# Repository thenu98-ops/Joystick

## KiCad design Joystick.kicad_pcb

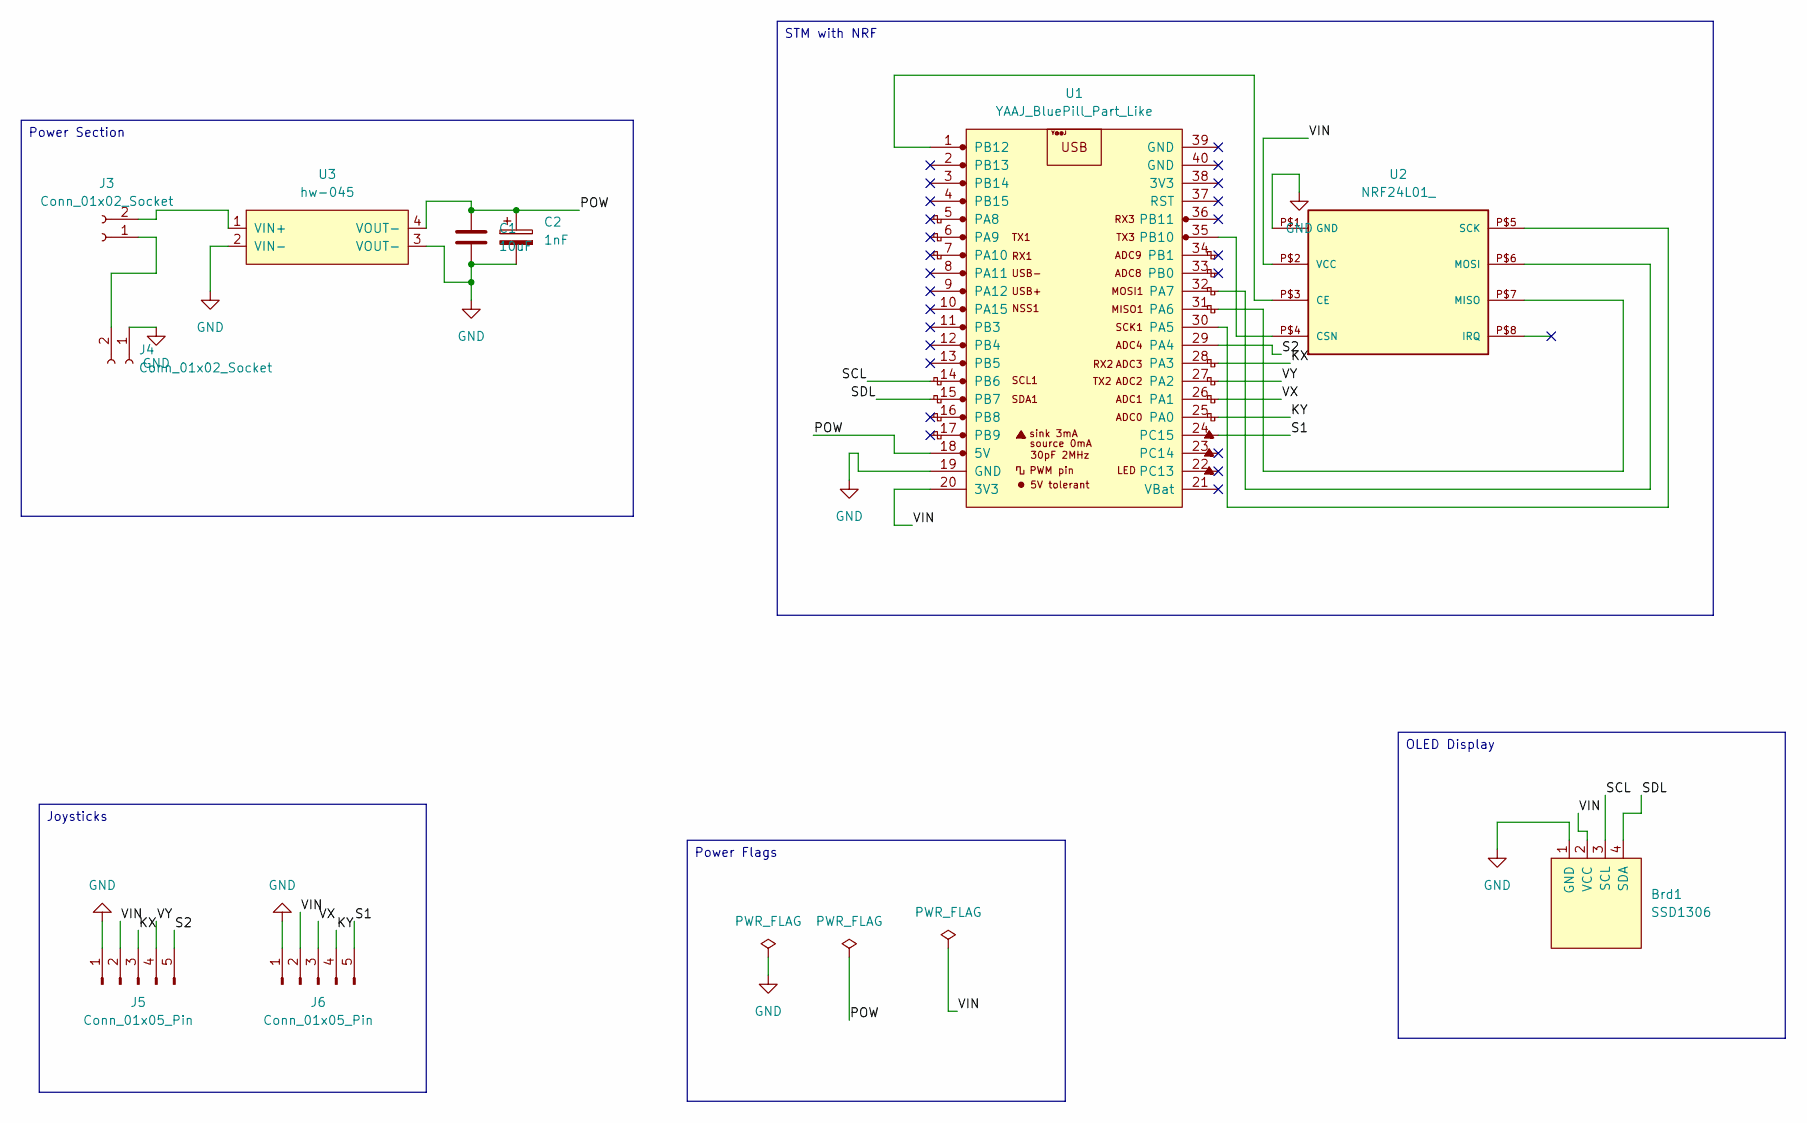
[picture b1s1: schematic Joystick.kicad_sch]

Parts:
Brd1: SSD1306; 128x64OLED
C1: 10uF; CP_Elec_4x5.4
C2: 1nF; CP_Radial_D4.0mm_P1.50mm
J3, J4: Conn_01x02_Socket; PinHeader_1x02_P2.54mm_Horizontal
J5, J6: Conn_01x05_Pin; PinHeader_1x05_P2.54mm_Horizontal
U1: YAAJ_BluePill_Part_Like; YAAJ_BluePill_1
U2: NRF24L01_; NRF24L01-PCB-AERIAL
U3: hw-045

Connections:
/KX: J5.3, U1.28 (PA3)
/KY: J6.4, U1.25 (PA0)
/POW: C1.1, C2.1, U1.18 (5V), U3.4 (VOUT-)
/S1: J6.5, U1.24 (PC15)
/S2: J5.5, U1.29 (PA4)
/SCL: Brd1.3 (SCL), U1.14 (PB6)
/SDL: Brd1.4 (SDA), U1.15 (PB7)
/VIN: Brd1.2 (VCC), J5.2, J6.2, U1.20 (3V3), U2.P$2 (VCC)
/VX: J6.3, U1.26 (PA1)
/VY: J5.4, U1.27 (PA2)
GND: Brd1.1 (GND), C1.2, C2.2, J4.1, J5.1, J6.1, U1.19 (GND), U2.P$1 (GND), U3.2 (VIN-), U3.3 (VOUT-)
unnamed: J3.1, J4.2
unnamed: J3.2, U3.1 (VIN+)
unnamed: U1.30 (PA5), U2.P$5 (SCK)
unnamed: U1.31 (PA6), U2.P$7 (MISO)
unnamed: U1.32 (PA7), U2.P$6 (MOSI)
unnamed: U1.35 (PB10), U2.P$4 (CSN)
unnamed: U1.1 (PB12), U2.P$3 (CE)

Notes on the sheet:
Power Section
STM with NRF
Joysticks
OLED Display
Power Flags

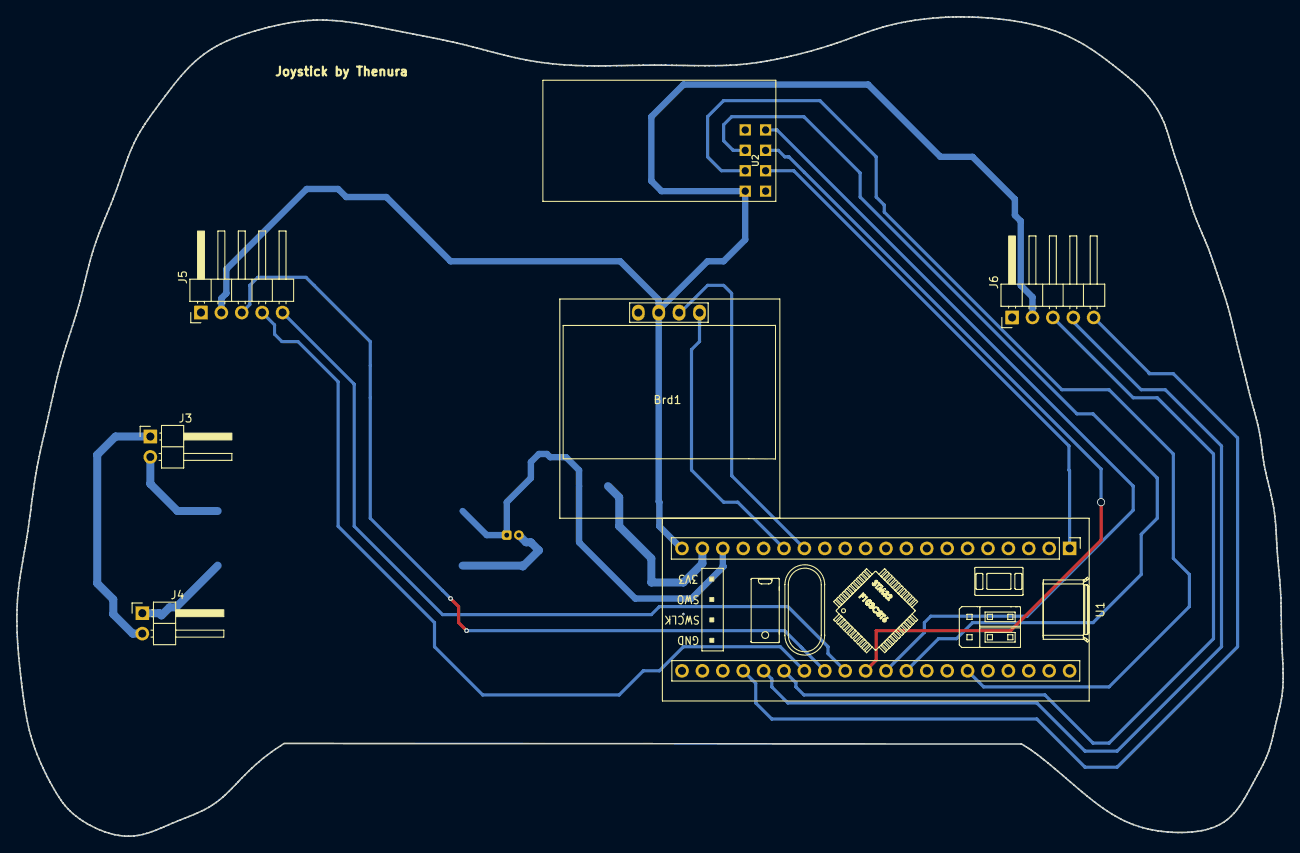
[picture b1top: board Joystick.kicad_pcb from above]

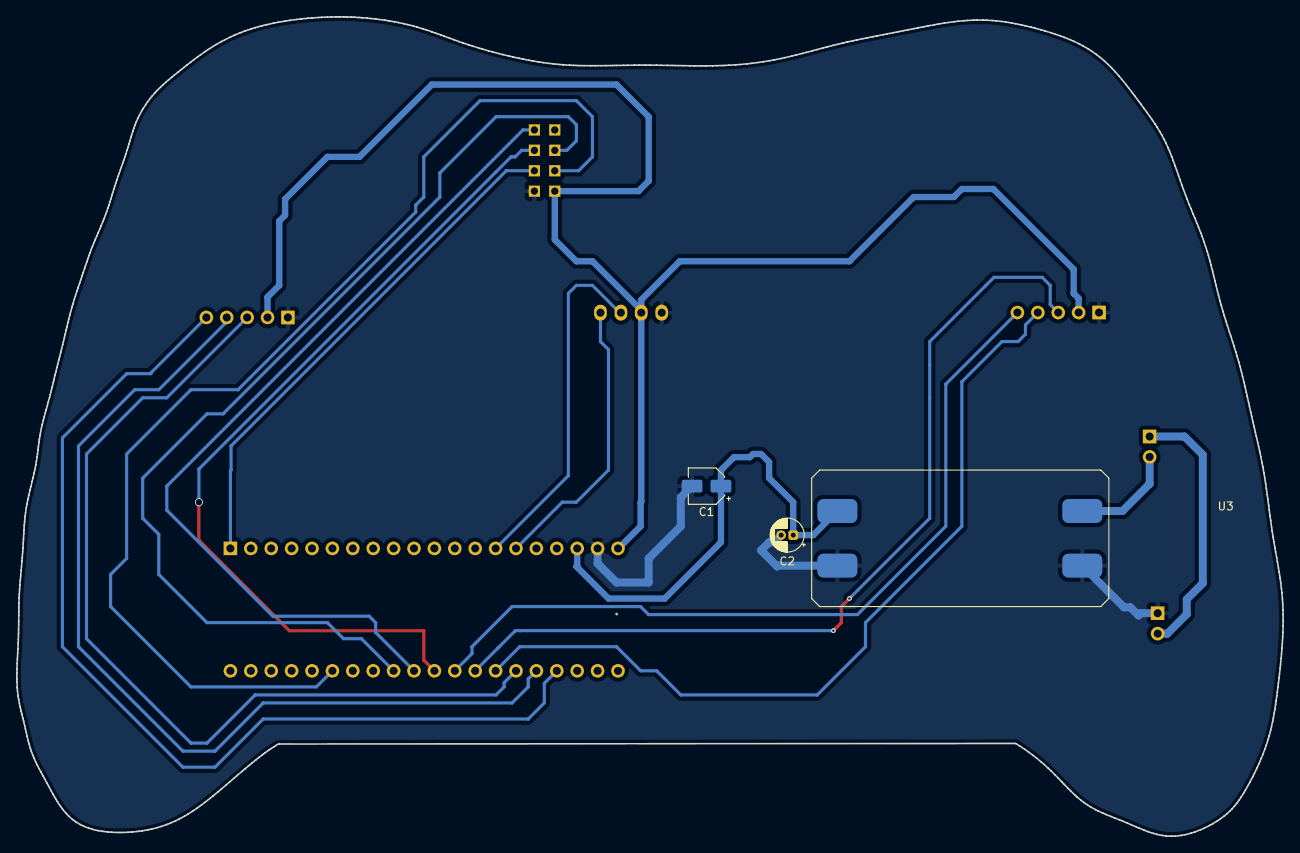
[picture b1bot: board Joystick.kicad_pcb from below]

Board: 2 copper layers, 157.7 x 102.0 mm, 10 parts (3 on the bottom side), 18 nets.

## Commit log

2025-07-09 production ready
2025-08-11 stmcube project
